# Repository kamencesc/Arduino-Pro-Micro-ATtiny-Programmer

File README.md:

# Arduino Pro Micro ATtiny85 Programmer
Board to program ATtiny85 using an Arduino Pro Micro.

It fits on two diferent size of Pro Micro (you can differenciate them by the USB, Mini USB for the big one and Micro USB for the little one).

Project comes from [Programming ATtiny85 with Arduino Uno ](https://create.arduino.cc/projecthub/arjun/programming-attiny85-with-arduino-uno-afb829) and it's adapted to Arduino Pro Micro, maybe needs some code modification (todo).

There are *OPTIONAL* LEDs as you can see in ~~[Utiliza tu placa Arduino como programador para ATtiny](https://fabricadigital.org/tutoriales/utiliza-tu-placa-arduino-como-programador-para-attiny/)~~ [Arduino as ISP and Arduino Bootloaders](https://docs.arduino.cc/built-in-examples/arduino-isp/ArduinoISP).

|LED|COLOR|FUNTION|
| -- | -- | -- |
|Top|Green|Heartbeat|
|Middle \*|Red|Error|
|Bottom \*|Yellow|Programming|

\* optional

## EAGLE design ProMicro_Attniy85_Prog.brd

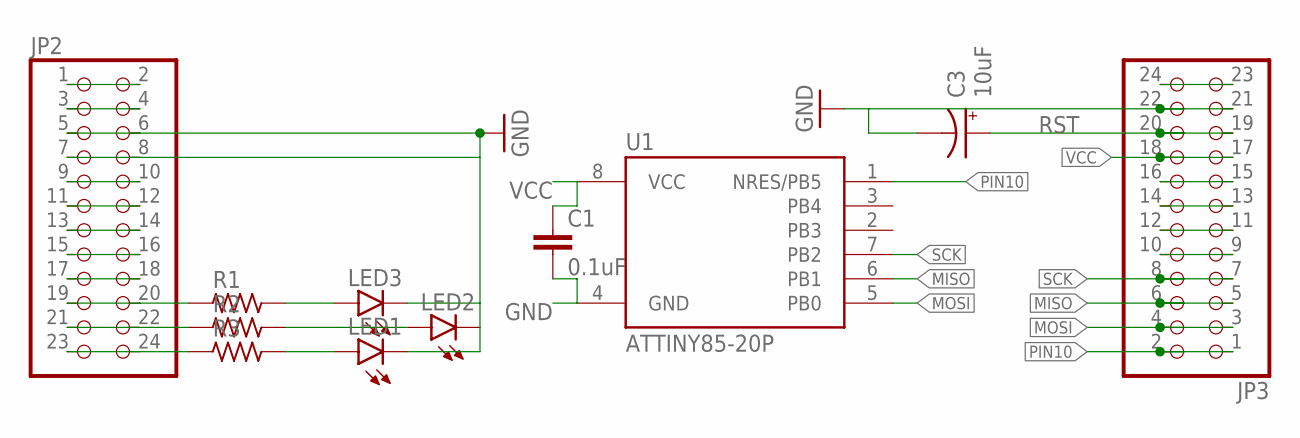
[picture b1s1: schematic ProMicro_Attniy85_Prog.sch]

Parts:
C1: 0.1uF; 0603
C3: 10uF; EIA3216
JP2, JP3: PINHD-2X12; 2X12
LED1, LED2, LED3: LEDCHIP-LED0805; CHIP-LED0805
R1, R2, R3: R_0805; R0805
U1: ATTINY85-20P; PDIP08_300MIL

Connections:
GND: C1.2, C3.-, JP2.5, JP2.6, JP2.7, JP2.8, JP3.21, JP3.22, LED1.C, LED2.C, LED3.C, U1.4 (GND)
MISO: JP3.5, JP3.6, U1.6 (PB1)
MOSI: JP3.3, JP3.4, U1.5 (PB0)
unnamed: JP2.1, JP2.2
unnamed: JP2.3, JP2.4
unnamed: JP2.9, JP2.10
unnamed: JP2.11, JP2.12
unnamed: JP2.13, JP2.14
unnamed: JP2.15, JP2.16
unnamed: JP2.17, JP2.18
unnamed: LED3.A, R1.2
unnamed: LED2.A, R2.2
unnamed: LED1.A, R3.2
unnamed: JP3.9, JP3.10
unnamed: JP3.11, JP3.12
unnamed: JP3.13, JP3.14
unnamed: JP3.15, JP3.16
unnamed: JP3.23, JP3.24
PIN7: JP2.19, JP2.20, R1.1
PIN8: JP2.21, JP2.22, R2.1
PIN9: JP2.23, JP2.24, R3.1
PIN10: JP3.1, JP3.2, U1.1 (NRES/PB5)
RST: C3.+, JP3.19, JP3.20
SCK: JP3.7, JP3.8, U1.7 (PB2)
VCC: C1.1, JP3.17, JP3.18, U1.8 (VCC)

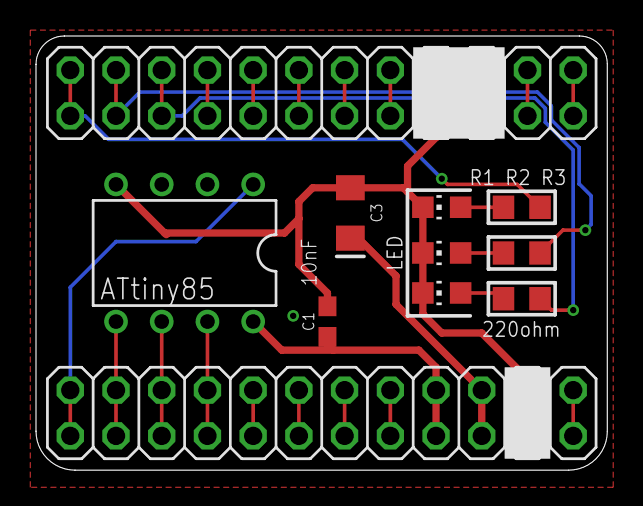
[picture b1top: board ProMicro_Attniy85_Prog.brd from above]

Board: 2 copper layers, 31.7 x 24.1 mm, 11 parts (0 on the bottom side), 25 nets.

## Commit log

2019-07-26 Add files via upload
    V1
2019-07-26 Add files via upload
    LEDs added following the desing in [Utiliza tu placa Arduino como programador para ATtiny]https://fabricadigital.org/tutoriales/utiliza-tu-placa-arduino-como-programador-para-attiny/
2019-07-26 Add files via upload
    minor changes
2019-07-26 Add files via upload
    pcb update
2019-08-12 Add files via upload
    Wrong size, corrected... the old one only fits on the original pro micro with micro USB
2022-03-12 Update README.md
    LED Info updated, broken links.
2022-03-14 Add files via upload
    As a recommendation from the AttinyCore85 Documentation, I've exchanged the capacitor (that was low) to an tantalum polar 100uf, and added another one of 0.1uf as coupler.

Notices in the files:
parts and their libraries:
rc-master-smd: Copyright (C) 2007, Bob Starr
SparkFun-Capacitors: Licensing: Creative Commons ShareAlike 4.0 International - https://creativecommons.org/licenses/by-sa/4.0
